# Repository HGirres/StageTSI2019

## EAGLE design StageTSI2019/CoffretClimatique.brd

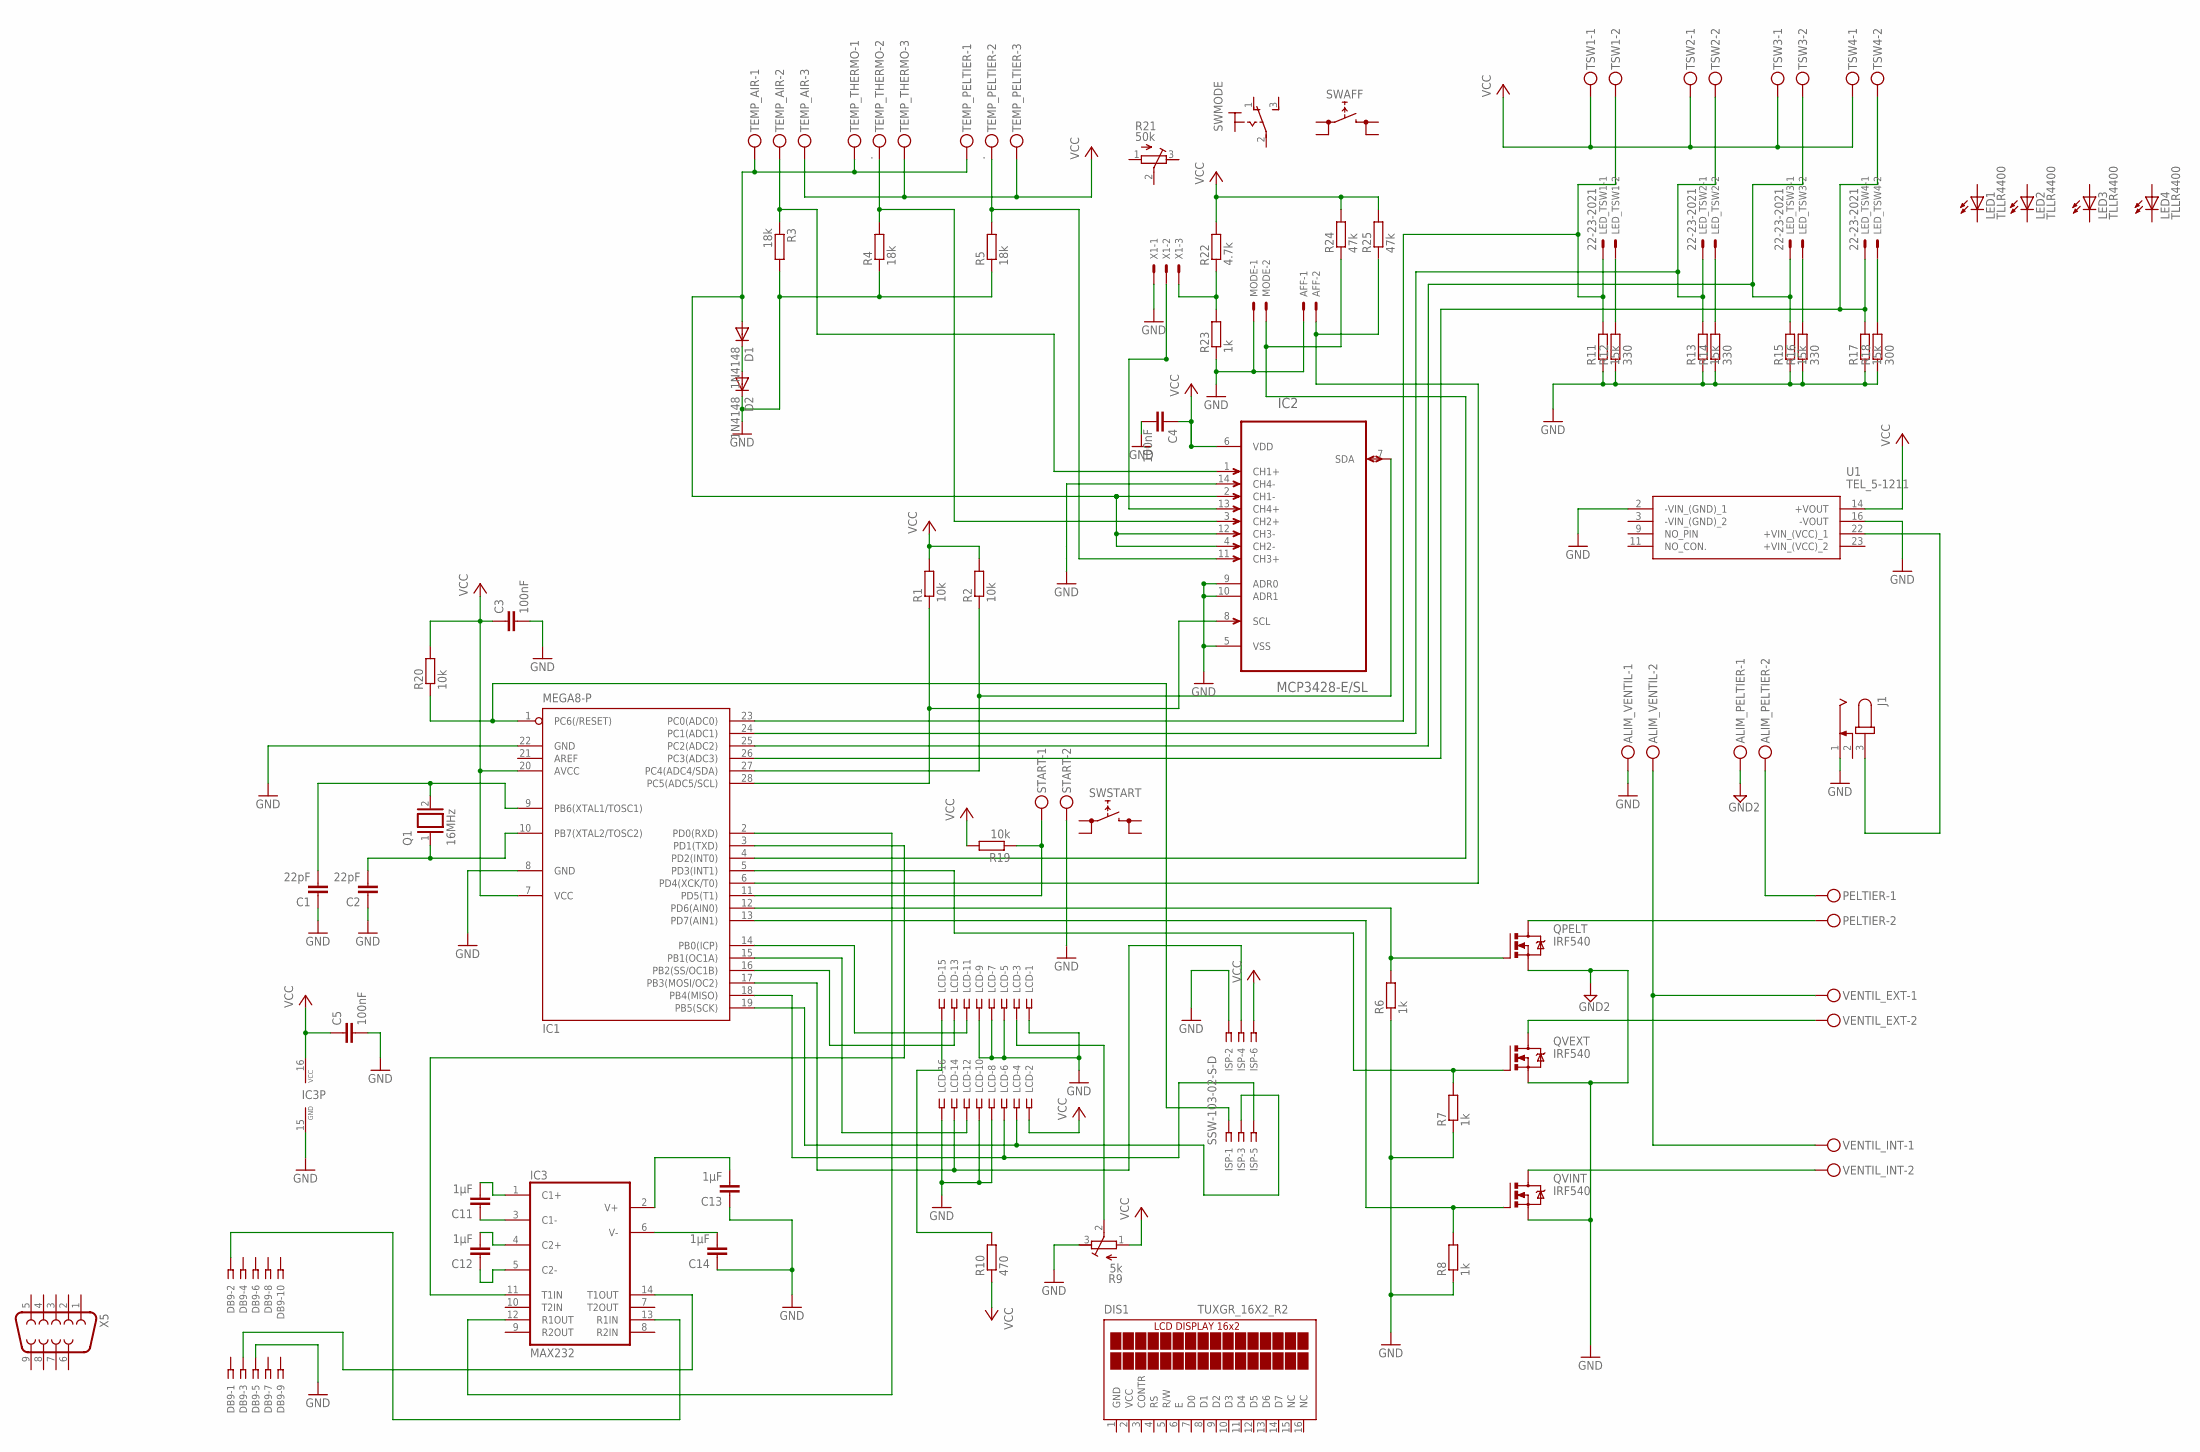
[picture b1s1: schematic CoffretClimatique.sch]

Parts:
AFF: 22-23-2021
ALIM_PELTIER: MKDSN1,5/2-5,08
ALIM_VENTIL: MKDSN1,5/2-5,08
C1, C2: 22pF; C075-032X103
C3, C4, C5: 100nF; C1206
C11, C12, C13, C14: 1µF; C1206
D1, D2: 1N4148; DO35-10
DB9: SSW-105-02-S-D
DIS1: TUXGR_16X2_R2
IC1: MEGA8-P; DIL28-3
IC2: MCP3428-E/SL; SOIC127P600X175-14N
IC3: MAX232; DIL16
ISP: SSW-103-02-S-D
J1: JACK-PLUG1; SPC4078
LCD: SSW-108-02-S-D
LED1, LED2, LED3, LED4: TLLR4400; LED3MM
LED_TSW1, LED_TSW2, LED_TSW3, LED_TSW4: 22-23-2021
MODE: 22-23-2021
PELTIER: MKDSN1,5/2-5,08
Q1: 16MHz; QS
QPELT: IRF540; TO220BV
QVEXT: IRF540; TO220BV
QVINT: IRF540; TO220BV
R1, R2: 10k; R0805
R3, R4, R5: 18k; 0207/10
R6, R7, R8, R23: 1k; 0207/10
R9: 5k; RTRIM64P
R10: 470; 0207/10
R11, R13, R15, R17: 15k; 0207/10
R12, R14, R16: 330; 0207/10
R18: 300; 0207/10
R19, R20: 10k; 0207/10
R21: 50k; RTRIM3296X
R22: 4.7k; 0207/10
R24, R25: 47k; 0207/10
START: MKDSN1,5/2-5,08
SWAFF: REKN
SWMODE: M9040P
SWSTART: REKN
TEMP_AIR: MKDSN1,5/3-5,08
TEMP_PELTIER: .; MKDSN1,5/3-5,08
TEMP_THERMO: .; MKDSN1,5/3-5,08
TSW1, TSW2, TSW3, TSW4: MKDSN1,5/2-5,08
U1: TEL_5-1211; TEL-5-1211
VENTIL_EXT: MKDSN1,5/2-5,08
VENTIL_INT: MKDSN1,5/2-5,08
X1: 22-23-2031
X5: F09V

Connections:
GND: AFF.1, ALIM_VENTIL.1, C1.1, C2.1, C3.2, C4.2, C5.2, C13.1, C14.1, D2.C, DB9.5, DIS1.1 (GND), IC1.8 (GND), IC1.22 (GND), IC2.5 (VSS), IC2.9 (ADR0), IC2.10 (ADR1), IC2.14 (CH4-), IC3.15 (GND), ISP.2, J1.1, LCD.1, LCD.5, LCD.7, LCD.8, LCD.9, LCD.10, LCD.16, MODE.1, QPELT.S, QVEXT.S, QVINT.S, R3.2, R4.1, R5.1, R6.1, R7.1, R8.1, R9.3 (E), R11.1, R12.1, R13.1, R14.1, R15.1, R16.1, R17.1, R18.1, R23.1, START.2, U1.2 (-VIN_(GND)_1), U1.16 (-VOUT), X1.1
GND2: ALIM_PELTIER.1
unnamed: C1.2, IC1.9 (PB6(XTAL1/TOSC1)), Q1.2
unnamed: C2.2, IC1.10 (PB7(XTAL2/TOSC2)), Q1.1
unnamed: J1.3, U1.22 (+VIN_(VCC)_1)
unnamed: QVEXT.D, VENTIL_EXT.2
unnamed: IC1.27 (PC4(ADC4/SDA)), IC2.7 (SDA), R2.1
unnamed: IC1.28 (PC5(ADC5/SCL)), IC2.8 (SCL), R1.1
unnamed: D1.C, D2.A
unnamed: ALIM_PELTIER.2, PELTIER.1
unnamed: IC2.1 (CH1+), R3.1, TEMP_AIR.2
unnamed: IC2.3 (CH2+), R4.2, TEMP_THERMO.2
unnamed: IC2.11 (CH3+), R5.2, TEMP_PELTIER.2
unnamed: D1.A, IC2.2 (CH1-), IC2.4 (CH2-), IC2.12 (CH3-), TEMP_AIR.1, TEMP_PELTIER.1, TEMP_THERMO.1
unnamed: IC2.13 (CH4+), X1.2
unnamed: PELTIER.2, QPELT.D
unnamed: ALIM_VENTIL.2, VENTIL_EXT.1, VENTIL_INT.1
unnamed: IC1.12 (PD6(AIN0)), QPELT.G, R6.2
unnamed: IC1.5 (PD3(INT1)), QVEXT.G, R7.2
unnamed: IC1.3 (PD1(TXD)), IC3.11 (T1IN)
unnamed: QVINT.D, VENTIL_INT.2
unnamed: DB9.2, IC3.13 (R1IN)
unnamed: LCD.3, R9.2 (S)
unnamed: DB9.3, IC3.14 (T1OUT)
unnamed: LCD.15, R10.2
unnamed: R22.1, R23.2, X1.3
unnamed: IC1.4 (PD2(INT0)), MODE.2, R24.1
unnamed: AFF.2, IC1.6 (PD4(XCK/T0)), R25.1
unnamed: IC1.11 (PD5(T1)), R19.1, START.1
unnamed: IC1.2 (PD0(RXD)), IC3.12 (R1OUT)
unnamed: IC1.13 (PD7(AIN1)), QVINT.G, R8.2
unnamed: IC1.23 (PC0(ADC0)), LED_TSW1.1, R11.2, TSW1.2
unnamed: IC1.19 (PB5(SCK)), ISP.3, LCD.4
unnamed: IC1.24 (PC1(ADC1)), LED_TSW2.1, R13.2, TSW2.2
unnamed: IC1.18 (PB4(MISO)), ISP.5, LCD.6
unnamed: IC1.25 (PC2(ADC2)), LED_TSW3.1, R15.2, TSW3.2
unnamed: IC1.14 (PB0(ICP)), LCD.11
unnamed: IC1.26 (PC3(ADC3)), LED_TSW4.1, R17.2, TSW4.2
unnamed: IC1.15 (PB1(OC1A)), LCD.12
unnamed: IC1.16 (PB2(SS/OC1B)), LCD.13
unnamed: LED_TSW1.2, R12.2
unnamed: LED_TSW2.2, R14.2
unnamed: LED_TSW3.2, R16.2
unnamed: LED_TSW4.2, R18.2
unnamed: IC1.17 (PB3(MOSI/OC2)), ISP.4, LCD.14
unnamed: IC1.1 (PC6(/RESET)), ISP.1, R20.1
unnamed: C11.2, IC3.1 (C1+)
unnamed: C11.1, IC3.3 (C1-)
unnamed: C12.2, IC3.4 (C2+)
unnamed: C12.1, IC3.5 (C2-)
unnamed: C14.2, IC3.6 (V-)
unnamed: C13.2, IC3.2 (V+)
VCC: C3.1, C4.1, C5.1, DIS1.2 (VCC), IC1.7 (VCC), IC1.20 (AVCC), IC2.6 (VDD), IC3.16 (VCC), ISP.6, LCD.2, R1.2, R2.2, R9.1 (A), R10.1, R19.2, R20.2, R22.2, R24.2, R25.2, TEMP_AIR.3, TEMP_PELTIER.3, TEMP_THERMO.3, TSW1.1, TSW2.1, TSW3.1, TSW4.1, U1.14 (+VOUT)

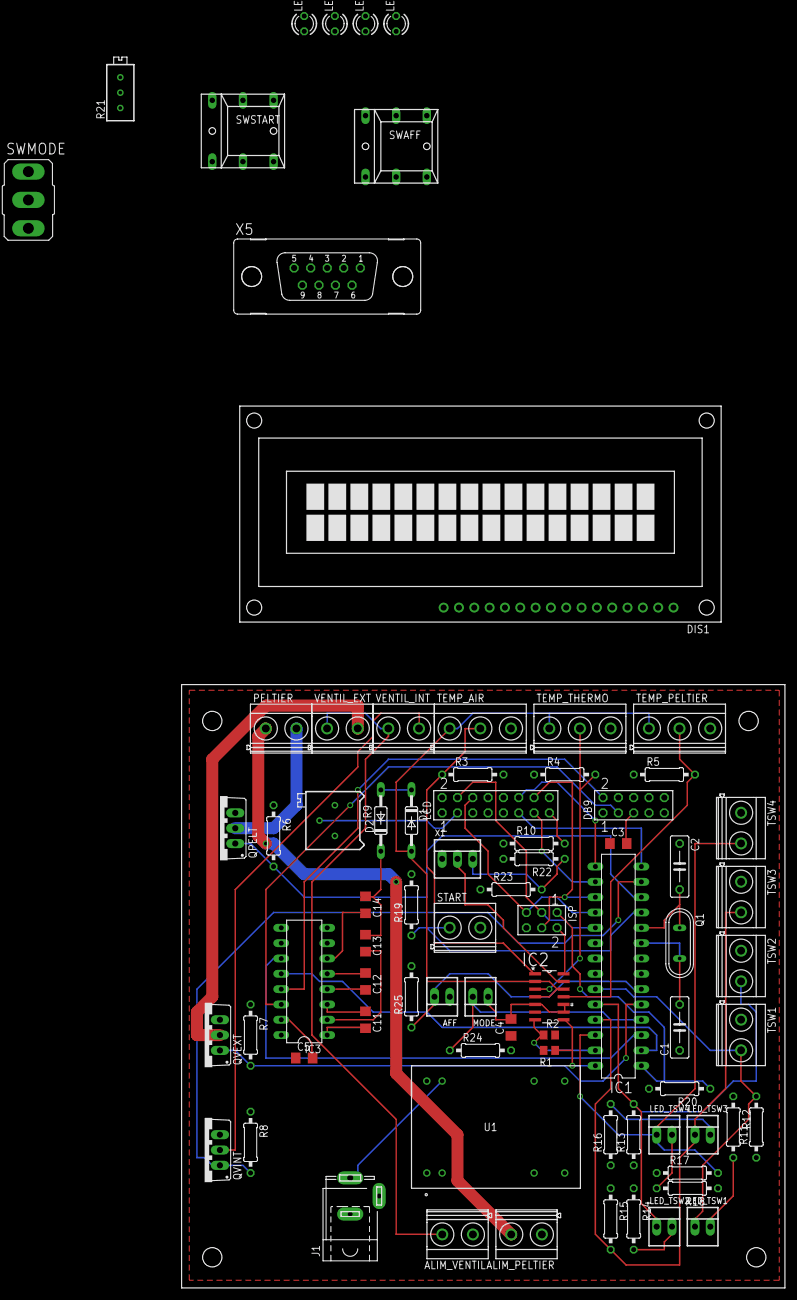
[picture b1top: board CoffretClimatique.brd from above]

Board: 2 copper layers, 100.0 x 100.0 mm, 77 parts (0 on the bottom side), 52 nets.

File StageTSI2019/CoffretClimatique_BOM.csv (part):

Partlist,exported,from,C:/Users/herve/Documents/eagle/StageTSI2019/StageTSI2019/CoffretClimatique.sch,at,23/04/2020,18:10:53,,,,,,,,,,,,,,,,,,,,,,,,,,,,,,,,,,,,,,,,,,,,,,,,,,,,
,,,,,,,,,,,,,,,,,,,,,,,,,,,,,,,,,,,,,,,,,,,,,,,,,,,,,,,,,,
Part,Value,Device,Package,Description,ALLIED_NUMBER,ALLIED_PRICE-STOCK,DESCRIPTION,HEIGHT,MANUFACTURER_NAME,MANUFACTURER_PART_NUMBER,MF,MOUSER_PART_NUMBER,MOUSER_PRICE-STOCK,MPN,OC_FARNELL,OC_NEWARK,PACKAGE,RS_PART_NUMBER,RS_PRICE-STOCK,SUPPLIER,,,,,,,,,,,,,,,,,,,,,,,,,,,,,,,,,,,,,,
AFF,22-23-2021,22-23-2021,".100""",(2.54mm),Center,Header,-,2,Pin,MOLEX,22-23-2021,1462926,25C3832,,,,,,,,,,,,,,,,,,,,,,,,,,,,,,,,,,,,,,,,,,,,,
ALIM_PELTIER,MKDSN1,5/2-5,8,MKDSN1,5/2-5,8,MKDSN,1,5/,2-5,8,Printklemme,MKDSN,1,5/2-5.08,1792903,30M2397,,,,,,,,,,,,,,,,,,,,,,,,,,,,,,,,,,,,,,,,,
ALIM_VENTIL,MKDSN1,5/2-5,8,MKDSN1,5/2-5,8,MKDSN,1,5/,2-5,8,Printklemme,MKDSN,1,5/2-5.08,1792903,30M2397,,,,,,,,,,,,,,,,,,,,,,,,,,,,,,,,,,,,,,,,,
C1,22pF,C-EU075-032X103,C075-032X103,CAPACITOR,European,symbol,,,,,,,,,,,,,,,,,,,,,,,,,,,,,,,,,,,,,,,,,,,,,,,,,,,,
C2,22pF,C-EU075-032X103,C075-032X103,CAPACITOR,European,symbol,,,,,,,,,,,,,,,,,,,,,,,,,,,,,,,,,,,,,,,,,,,,,,,,,,,,
C3,100nF,C-EUC1206,C1206,CAPACITOR,European,symbol,,,,,,,,,,,,,,,,,,,,,,,,,,,,,,,,,,,,,,,,,,,,,,,,,,,,
C4,100nF,C-EUC1206,C1206,CAPACITOR,European,symbol,,,,,,,,,,,,,,,,,,,,,,,,,,,,,,,,,,,,,,,,,,,,,,,,,,,,
C5,100nF,C-EUC1206,C1206,CAPACITOR,European,symbol,,,,,,,,,,,,,,,,,,,,,,,,,,,,,,,,,,,,,,,,,,,,,,,,,,,,
C11,1µF,C-EUC1206,C1206,CAPACITOR,European,symbol,,,,,,,,,,,,,,,,,,,,,,,,,,,,,,,,,,,,,,,,,,,,,,,,,,,,
C12,1µF,C-EUC1206,C1206,CAPACITOR,European,symbol,,,,,,,,,,,,,,,,,,,,,,,,,,,,,,,,,,,,,,,,,,,,,,,,,,,,
C13,1µF,C-EUC1206,C1206,CAPACITOR,European,symbol,,,,,,,,,,,,,,,,,,,,,,,,,,,,,,,,,,,,,,,,,,,,,,,,,,,,
C14,1µF,C-EUC1206,C1206,CAPACITOR,European,symbol,,,,,,,,,,,,,,,,,,,,,,,,,,,,,,,,,,,,,,,,,,,,,,,,,,,,
D1,1N4148,1N4148DO35-10,DO35-10,DIODE,,,,,,,,,,,,,,,,,,,,,,,,,,,,,,,,,,,,,,,,,,,,,,,,,,,,,,
D2,1N4148,1N4148DO35-10,DO35-10,DIODE,,,,,,,,,,,,,,,,,,,,,,,,,,,,,,,,,,,,,,,,,,,,,,,,,,,,,,
DB9,SSW-105-02-S-D,SSW-105-02-S-D,THROUGH-HOLE,".025""",SQ,POST,SOCKET,SSW-105-02-S-D,unknown,11P9398,,,,,,,,,,,,,,,,,,,,,,,,,,,,,,,,,,,,,,,,,,,,,,,,
DIS1,TUXGR_16X2_R2,TUXGR_16X2_R2,TUXGR_16X2_R2,Tuxgraphics,LCD,display,16x2,characters,reflective,without,background,light,unknown,unknown,,,,,,,,,,,,,,,,,,,,,,,,,,,,,,,,,,,,,,,,,,,,
IC1,MEGA8-P,MEGA8-P,DIL28-3,MICROCONTROLLER,unknown,unknown,,,,,,,,,,,,,,,,,,,,,,,,,,,,,,,,,,,,,,,,,,,,,,,,,,,,
IC2,MCP3428-E/SL,MCP3428-E/SL,SOIC127P600X175-14N,Analog-to-Digital,Converter,MCP3428-E/SL,1825014,52R9962,SOIC-14,Microchip,,,,,,,,,,,,,,,,,,,,,,,,,,,,,,,,,,,,,,,,,,,,,,,,
IC3,MAX232,MAX232,DIL16,RS232,TRANSEIVER,MAXIM,MAX232ACPE+,9723773,68K4544,,,,,,,,,,,,,,,,,,,,,,,,,,,,,,,,,,,,,,,,,,,,,,,,,
ISP,SSW-103-02-S-D,SSW-103-02-S-D,SSW-103-02-S-D,THROUGH-HOLE,".025""",SQ,POST,SOCKET,SSW-103-02-S-D,unknown,11P9365,,,,,,,,,,,,,,,,,,,,,,,,,,,,,,,,,,,,,,,,,,,,,,,
J1,JACK-PLUG1,SPC4078,DC,POWER,JACK,unknown,unknown,,,,,,,,,,,,,,,,,,,,,,,,,,,,,,,,,,,,,,,,,,,,,,,,,,,
LCD,SSW-108-02-S-D,SSW-108-02-S-D,THROUGH-HOLE,".025""",SQ,POST,SOCKET,SSW-108-02-S-D,unknown,85K7646,,,,,,,,,,,,,,,,,,,,,,,,,,,,,,,,,,,,,,,,,,,,,,,,
LED1,TLLR4400,TLLR4400,LED3MM,Low,Current,(2mA),LED,3,mm,Tinted,Diffused,Package,color,RED,VISHAY,SEMICONDUCTOR,1612437,,,,,,,,,,,,,,,,,,,,,,,,,,,,,,,,,,,,,,,,,
LED2,TLLR4400,TLLR4400,LED3MM,Low,Current,(2mA),LED,3,mm,Tinted,Diffused,Package,color,RED,VISHAY,SEMICONDUCTOR,1612437,,,,,,,,,,,,,,,,,,,,,,,,,,,,,,,,,,,,,,,,,
LED3,TLLR4400,TLLR4400,LED3MM,Low,Current,(2mA),LED,3,mm,Tinted,Diffused,Package,color,RED,VISHAY,SEMICONDUCTOR,1612437,,,,,,,,,,,,,,,,,,,,,,,,,,,,,,,,,,,,,,,,,
LED4,TLLR4400,TLLR4400,LED3MM,Low,Current,(2mA),LED,3,mm,Tinted,Diffused,Package,color,RED,VISHAY,SEMICONDUCTOR,1612437,,,,,,,,,,,,,,,,,,,,,,,,,,,,,,,,,,,,,,,,,
LED_TSW1,22-23-2021,22-23-2021,22-23-2021,".100""",(2.54mm),Center,Header,-,2,Pin,MOLEX,22-23-2021,1462926,25C3832,,,,,,,,,,,,,,,,,,,,,,,,,,,,,,,,,,,,,,,,,,,,
LED_TSW2,22-23-2021,22-23-2021,22-23-2021,".100""",(2.54mm),Center,Header,-,2,Pin,MOLEX,22-23-2021,1462926,25C3832,,,,,,,,,,,,,,,,,,,,,,,,,,,,,,,,,,,,,,,,,,,,
LED_TSW3,22-23-2021,22-23-2021,22-23-2021,".100""",(2.54mm),Center,Header,-,2,Pin,MOLEX,22-23-2021,1462926,25C3832,,,,,,,,,,,,,,,,,,,,,,,,,,,,,,,,,,,,,,,,,,,,
LED_TSW4,22-23-2021,22-23-2021,22-23-2021,".100""",(2.54mm),Center,Header,-,2,Pin,MOLEX,22-23-2021,1462926,25C3832,,,,,,,,,,,,,,,,,,,,,,,,,,,,,,,,,,,,,,,,,,,,
MODE,22-23-2021,22-23-2021,".100""",(2.54mm),Center,Header,-,2,Pin,MOLEX,22-23-2021,1462926,25C3832,,,,,,,,,,,,,,,,,,,,,,,,,,,,,,,,,,,,,,,,,,,,,
PELTIER,MKDSN1,5/2-5,8,MKDSN1,5/2-5,8,MKDSN,1,5/,2-5,8,Printklemme,MKDSN,1,5/2-5.08,1792903,30M2397,,,,,,,,,,,,,,,,,,,,,,,,,,,,,,,,,,,,,,,,,
Q1,16MHz,XTAL/S,QS,CRYSTAL,,,,,,,,,,,,,,,,,,,,,,,,,,,,,,,,,,,,,,,,,,,,,,,,,,,,,,
QPELT,IRF540,IRF540,TO220BV,HEXFET,Power,MOSFET,,,,,,,,,,,,,,,,,,,,,,,,,,,,,,,,,,,,,,,,,,,,,,,,,,,,
QVEXT,IRF540,IRF540,TO220BV,HEXFET,Power,MOSFET,,,,,,,,,,,,,,,,,,,,,,,,,,,,,,,,,,,,,,,,,,,,,,,,,,,,
QVINT,IRF540,IRF540,TO220BV,HEXFET,Power,MOSFET,,,,,,,,,,,,,,,,,,,,,,,,,,,,,,,,,,,,,,,,,,,,,,,,,,,,
R1,10k,R-EU_R0805,R0805,RESISTOR,European,symbol,,,,,,,,,,,,,,,,,,,,,,,,,,,,,,,,,,,,,,,,,,,,,,,,,,,,
R2,10k,R-EU_R0805,R0805,RESISTOR,European,symbol,,,,,,,,,,,,,,,,,,,,,,,,,,,,,,,,,,,,,,,,,,,,,,,,,,,,
R3,18k,R-EU_0207/10,0207/10,RESISTOR,European,symbol,,,,,,,,,,,,,,,,,,,,,,,,,,,,,,,,,,,,,,,,,,,,,,,,,,,,
R4,18k,R-EU_0207/10,0207/10,RESISTOR,European,symbol,,,,,,,,,,,,,,,,,,,,,,,,,,,,,,,,,,,,,,,,,,,,,,,,,,,,
R5,18k,R-EU_0207/10,0207/10,RESISTOR,European,symbol,,,,,,,,,,,,,,,,,,,,,,,,,,,,,,,,,,,,,,,,,,,,,,,,,,,,
R6,1k,R-EU_0207/10,0207/10,RESISTOR,European,symbol,,,,,,,,,,,,,,,,,,,,,,,,,,,,,,,,,,,,,,,,,,,,,,,,,,,,
R7,1k,R-EU_0207/10,0207/10,RESISTOR,European,symbol,,,,,,,,,,,,,,,,,,,,,,,,,,,,,,,,,,,,,,,,,,,,,,,,,,,,
R8,1k,R-EU_0207/10,0207/10,RESISTOR,European,symbol,,,,,,,,,,,,,,,,,,,,,,,,,,,,,,,,,,,,,,,,,,,,,,,,,,,,
R9,5k,R-TRIMM64P,RTRIM64P,Trimm,resistor,,,,,,,,,,,,,,,,,,,,,,,,,,,,,,,,,,,,,,,,,,,,,,,,,,,,,
R10,470,R-EU_0207/10,0207/10,RESISTOR,European,symbol,,,,,,,,,,,,,,,,,,,,,,,,,,,,,,,,,,,,,,,,,,,,,,,,,,,,
R11,15k,R-EU_0207/10,0207/10,RESISTOR,European,symbol,,,,,,,,,,,,,,,,,,,,,,,,,,,,,,,,,,,,,,,,,,,,,,,,,,,,
R12,330,R-EU_0207/10,0207/10,RESISTOR,European,symbol,,,,,,,,,,,,,,,,,,,,,,,,,,,,,,,,,,,,,,,,,,,,,,,,,,,,
R13,15k,R-EU_0207/10,0207/10,RESISTOR,European,symbol,,,,,,,,,,,,,,,,,,,,,,,,,,,,,,,,,,,,,,,,,,,,,,,,,,,,
R14,330,R-EU_0207/10,0207/10,RESISTOR,European,symbol,,,,,,,,,,,,,,,,,,,,,,,,,,,,,,,,,,,,,,,,,,,,,,,,,,,,
R15,15k,R-EU_0207/10,0207/10,RESISTOR,European,symbol,,,,,,,,,,,,,,,,,,,,,,,,,,,,,,,,,,,,,,,,,,,,,,,,,,,,
R16,330,R-EU_0207/10,0207/10,RESISTOR,European,symbol,,,,,,,,,,,,,,,,,,,,,,,,,,,,,,,,,,,,,,,,,,,,,,,,,,,,
R17,15k,R-EU_0207/10,0207/10,RESISTOR,European,symbol,,,,,,,,,,,,,,,,,,,,,,,,,,,,,,,,,,,,,,,,,,,,,,,,,,,,
R18,300,R-EU_0207/10,0207/10,RESISTOR,European,symbol,,,,,,,,,,,,,,,,,,,,,,,,,,,,,,,,,,,,,,,,,,,,,,,,,,,,
R19,10k,R-EU_0207/10,0207/10,RESISTOR,European,symbol,,,,,,,,,,,,,,,,,,,,,,,,,,,,,,,,,,,,,,,,,,,,,,,,,,,,
R20,10k,R-EU_0207/10,0207/10,RESISTOR,European,symbol,,,,,,,,,,,,,,,,,,,,,,,,,,,,,,,,,,,,,,,,,,,,,,,,,,,,
R21,50k,R-TRIMM3296X,RTRIM3296X,Trimm,resistor,,,,,,,,,,,,,,,,,,,,,,,,,,,,,,,,,,,,,,,,,,,,,,,,,,,,,
R22,4.7k,R-EU_0207/10,0207/10,RESISTOR,European,symbol,,,,,,,,,,,,,,,,,,,,,,,,,,,,,,,,,,,,,,,,,,,,,,,,,,,,
R23,1k,R-EU_0207/10,0207/10,RESISTOR,European,symbol,,,,,,,,,,,,,,,,,,,,,,,,,,,,,,,,,,,,,,,,,,,,,,,,,,,,
R24,47k,R-EU_0207/10,0207/10,RESISTOR,European,symbol,,,,,,,,,,,,,,,,,,,,,,,,,,,,,,,,,,,,,,,,,,,,,,,,,,,,
R25,47k,R-EU_0207/10,0207/10,RESISTOR,European,symbol,,,,,,,,,,,,,,,,,,,,,,,,,,,,,,,,,,,,,,,,,,,,,,,,,,,,
START,MKDSN1,5/2-5,8,MKDSN1,5/2-5,8,MKDSN,1,5/,2-5,8,Printklemme,MKDSN,1,5/2-5.08,1792903,30M2397,,,,,,,,,,,,,,,,,,,,,,,,,,,,,,,,,,,,,,,,,
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
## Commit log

2023-03-07 Version intiale
